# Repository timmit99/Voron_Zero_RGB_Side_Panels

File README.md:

# Voron Zero RGB Side Panels
 ## Side panels for the Voron Zero printer with 16 WS2812 RGB LED's per side.
 
 ### The build below has some [3mm TAP Plastic black LED acrylic](https://www.tapplastics.com/product/plastics/cut_to_size_plastic/black_led_sheet/668) installed INSIDE the frame extrusions to diffuse the LEDs. They are cut per the [DXF](/CAD/diffuserPanel.dxf) and the [PDF](/CAD/diffuserPanel.pdf) in the CAD folder. 
 
 #### NOTE: The notched corners are intended to go in the front corners to allow the panel to clear the bottom blind joint. My prefernce is to have the matte finish towards the inside of the printer as the glossy side is easy to scratch and scratches are very visible.

# I've published the files also over on PCBWays project site!
https://www.pcbway.com/project/shareproject/Voron_Zero_Side_Panel___Left.html

https://www.pcbway.com/project/shareproject/Voron_Zero_Side_Panel___Right.html

## Build steps
1. Order set of PCB's.
2. Order 32 5050 RGB/RGBW LED's.
3. Print replacement panel clips.
4. Assemble PCB's with your choice of 0.1" 6 pin connector (JST-XH, Dupont, bare wire).
5. Plug in and test.
6. DONE!

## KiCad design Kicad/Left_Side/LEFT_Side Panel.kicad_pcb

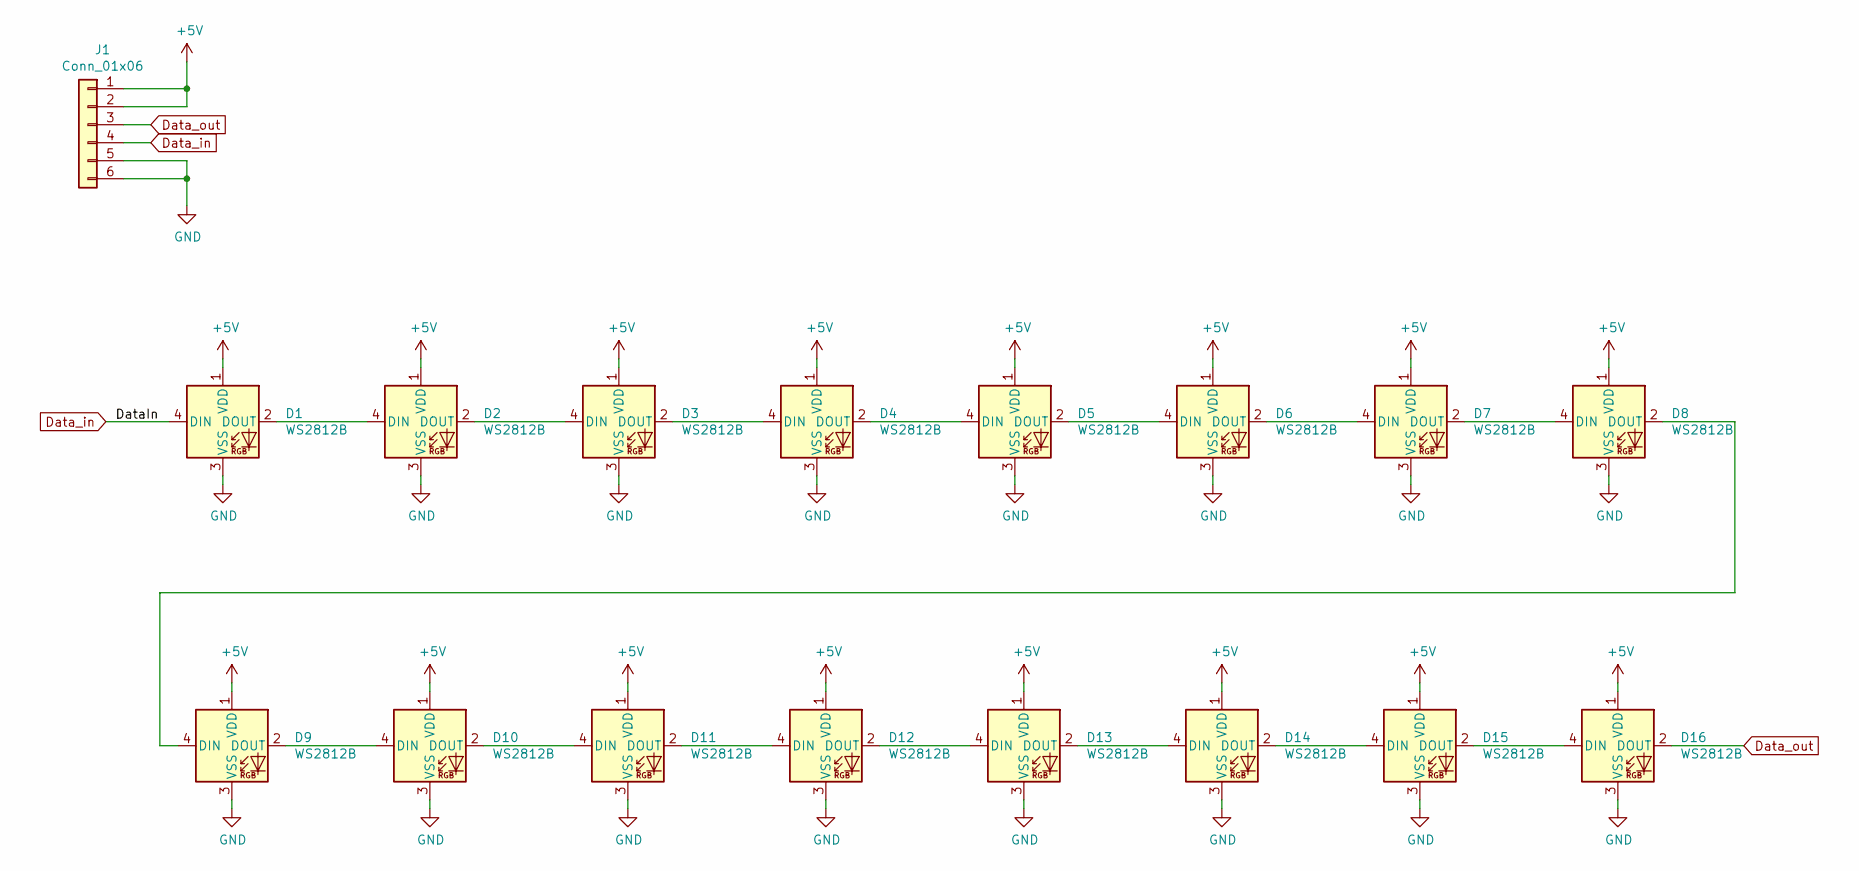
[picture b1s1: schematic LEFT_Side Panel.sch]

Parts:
D1, D2, D3, D4, D5, D6, D7, D8, D9, D10, D11, D12, D13, D14, D15, D16: WS2812B; LED_WS2812B_PLCC4_5.0x5.0mm_P3.2mm
J1: Conn_01x06; PinHeader_1x06_P2.54mm_Vertical

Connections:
+5V: D1.1 (VDD), D2.1 (VDD), D3.1 (VDD), D4.1 (VDD), D5.1 (VDD), D6.1 (VDD), D7.1 (VDD), D8.1 (VDD), D9.1 (VDD), D10.1 (VDD), D11.1 (VDD), D12.1 (VDD), D13.1 (VDD), D14.1 (VDD), D15.1 (VDD), D16.1 (VDD), J1.1, J1.2
Data_in: D1.4 (DIN), J1.4
Data_out: D16.2 (DOUT), J1.3
GND: D1.3 (VSS), D2.3 (VSS), D3.3 (VSS), D4.3 (VSS), D5.3 (VSS), D6.3 (VSS), D7.3 (VSS), D8.3 (VSS), D9.3 (VSS), D10.3 (VSS), D11.3 (VSS), D12.3 (VSS), D13.3 (VSS), D14.3 (VSS), D15.3 (VSS), D16.3 (VSS), J1.5, J1.6
unnamed: D1.2 (DOUT), D2.4 (DIN)
unnamed: D2.2 (DOUT), D3.4 (DIN)
unnamed: D3.2 (DOUT), D4.4 (DIN)
unnamed: D4.2 (DOUT), D5.4 (DIN)
unnamed: D5.2 (DOUT), D6.4 (DIN)
unnamed: D6.2 (DOUT), D7.4 (DIN)
unnamed: D7.2 (DOUT), D8.4 (DIN)
unnamed: D8.2 (DOUT), D9.4 (DIN)
unnamed: D10.2 (DOUT), D11.4 (DIN)
unnamed: D9.2 (DOUT), D10.4 (DIN)
unnamed: D11.2 (DOUT), D12.4 (DIN)
unnamed: D12.2 (DOUT), D13.4 (DIN)
unnamed: D13.2 (DOUT), D14.4 (DIN)
unnamed: D14.2 (DOUT), D15.4 (DIN)
unnamed: D15.2 (DOUT), D16.4 (DIN)

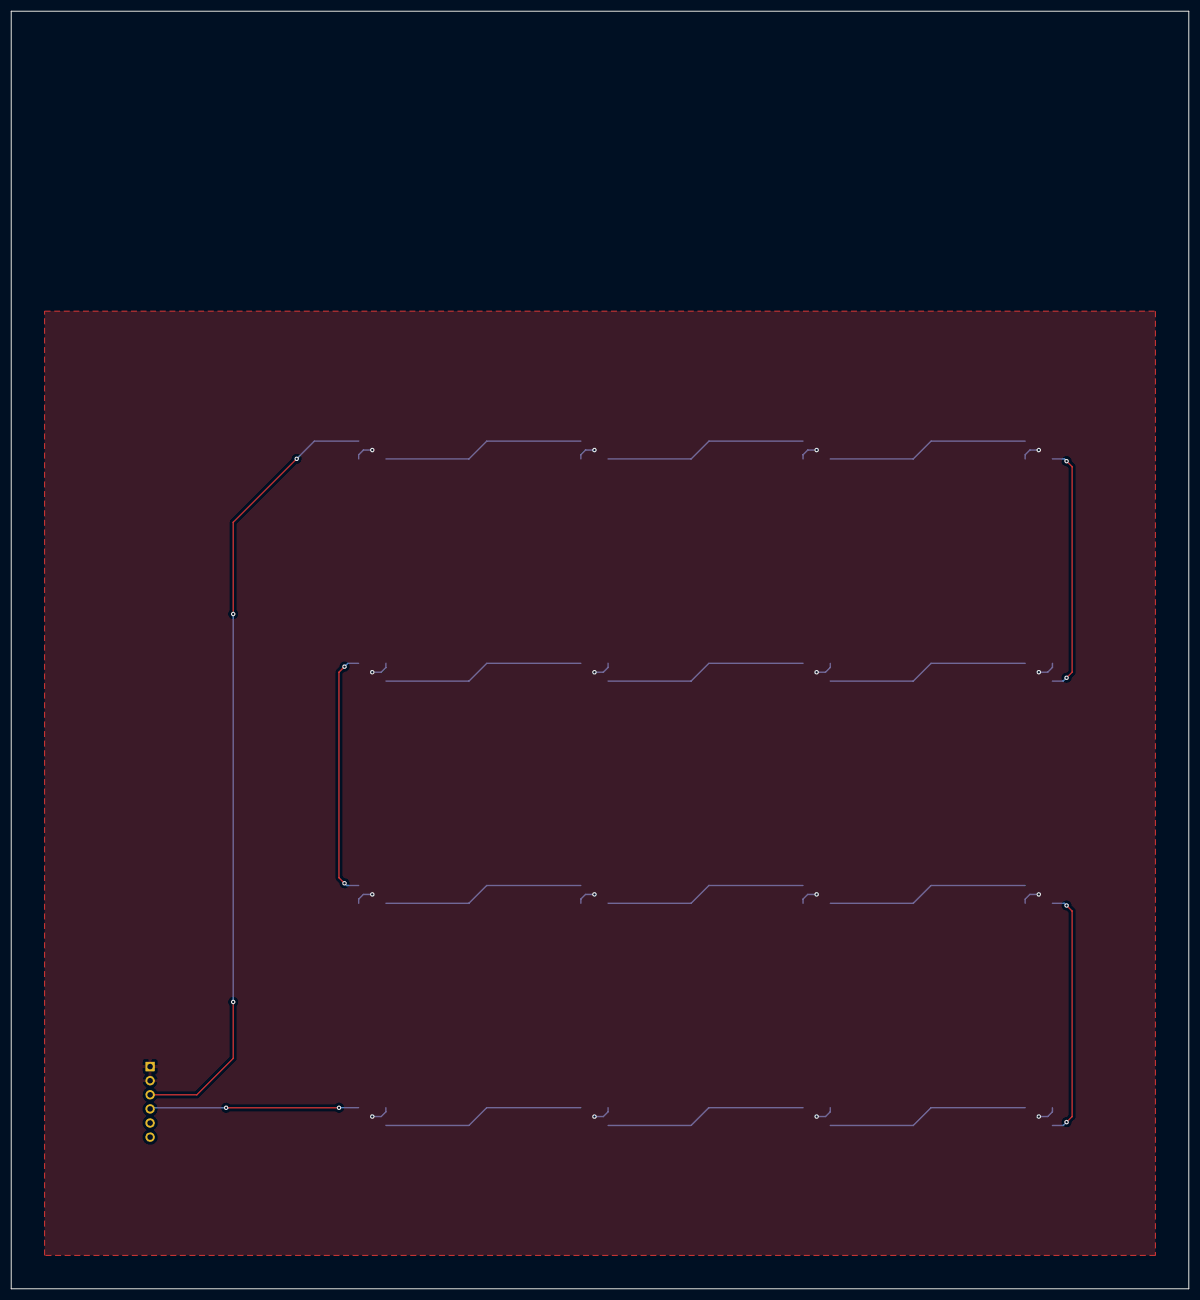
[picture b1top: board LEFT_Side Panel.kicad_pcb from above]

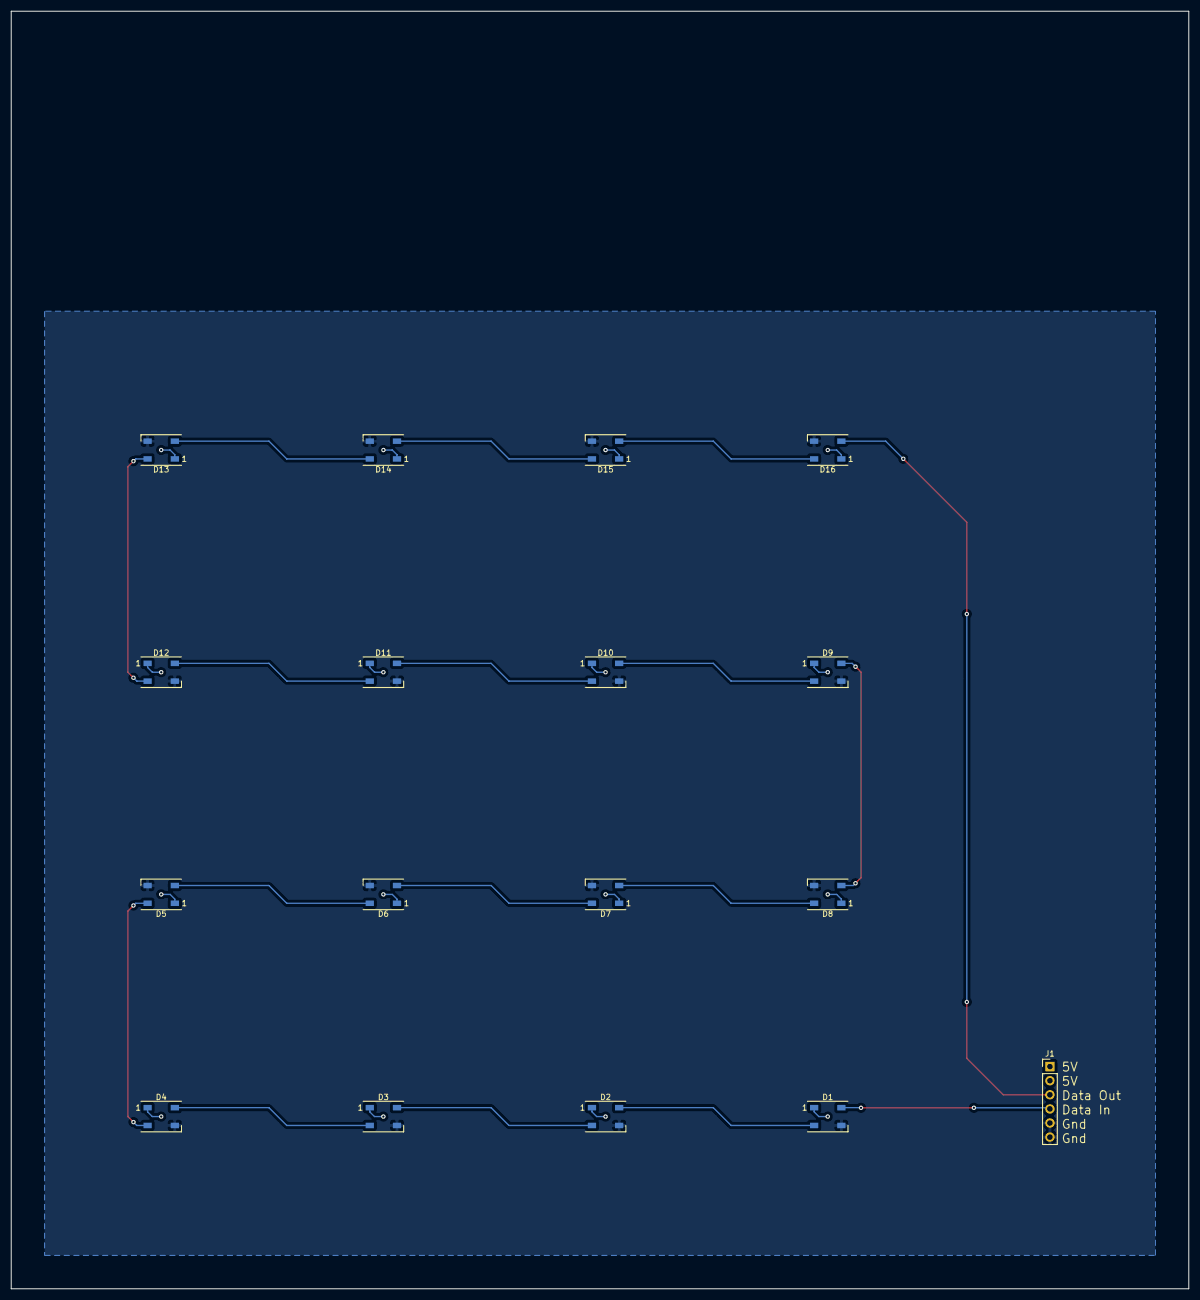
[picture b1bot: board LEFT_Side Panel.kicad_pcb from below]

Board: 2 copper layers, 212.0 x 230.0 mm, 17 parts (17 on the bottom side), 19 nets.

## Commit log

2021-11-28 Initial Commit of PCB's and CAD
2021-11-28 Add code examples for controlling with the Klipper RasPi
